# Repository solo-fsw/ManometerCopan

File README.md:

# ManometerCopan
Manometer for Copan lab

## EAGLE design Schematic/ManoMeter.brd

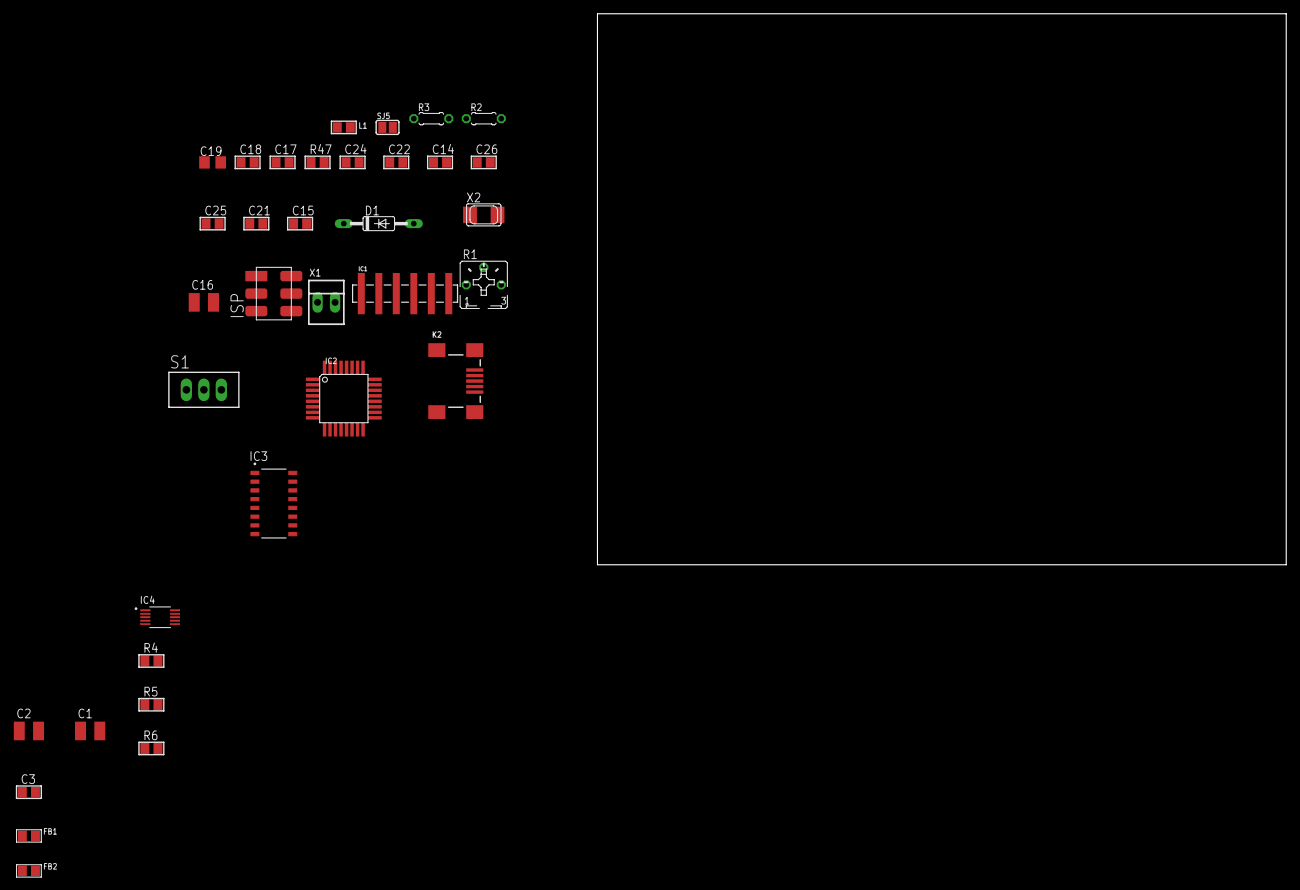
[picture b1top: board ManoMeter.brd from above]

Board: 2 copper layers, 100.0 x 80.0 mm, 35 parts (0 on the bottom side), 26 nets, no tracks yet.

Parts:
C1, C2, C16: 10u; C1210
C3, C14, C22, C24: 100n; C0805
C15, C21, C25, C26: 100N; C0805
C17, C18: 22p; C0805
C19: 10uF; R/2012-12R
D1: 1N4148DO35-10; DO35-10
FB1, FB2: MMZ2012Y152B; 0805
IC1: MPS20N0040D-S; 1X06_SMD_MALE
IC2: ATMEGA328P-32PIN-AU; TQFP32-08
IC3: CH340C; SOIC127P600X180-16N
IC4: ADS1115IDGST; SOP50P490X110-10N
ISP: 2X3P-2.54-SMD
K2: USB_MINI-B_SMT; USB-MINIB
L1: 10uH; 0805@1
R1: 10K; B25P
R2: 390; 0204/5
R3: 1k; 0204/5
R4, R5, R6: 4K7; M0805
R47: 10K; M0805
S1: Manual/Off/Auto; TL3XPO
SJ5: SOLDERJUMPER_REFLOW
X1: 22-23-2021
X2: 16Mhz; NX5032

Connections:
+5V: C1.1, C2.1, C3.2, C14.2, C16.1, C19.+, C22.2, C24.2, FB1.1, FB1.2, IC1.2, IC2.4, IC2.6, IC3.16, IC4.8, ISP.2, L1.2, R1.A, R4.2, R5.2, R6.2, R47.2, SJ5.2
AGND: C1.2, C3.1, FB2.2, IC1.5, IC4.3
GND: C2.2, C14.1, C15.2, C16.2, C17.2, C18.2, C19.-, C21.2, C22.1, C24.1, C26.2, D1.A, FB2.1, IC2.3, IC2.5, IC2.21, IC3.1, IC4.1, ISP.6, K2.GND, K2.S1, K2.S2, K2.S3, K2.S4, R1.E, R3.1, S1.2
unnamed: IC2.32, S1.3
unnamed: IC1.3, IC4.7
unnamed: IC1.1, IC1.6, IC4.6
unnamed: IC2.28, IC4.10, R6.1
unnamed: IC2.27, IC4.9, R5.1
unnamed: IC2.26, IC4.2, R4.1
unnamed: IC2.23, R1.S
unnamed: IC2.1, R2.1
unnamed: R2.2, R3.2
unnamed: D1.C, X1.2
unnamed: IC2.2, S1.1
unnamed: IC3.6, K2.D-
unnamed: C15.1, IC3.4
unnamed: C26.1, IC2.20
unnamed: C25.1, IC3.13
unnamed: IC3.5, K2.D+
unnamed: IC2.31, IC3.3
unnamed: K2.VBUS, SJ5.1
unnamed: C21.1, IC2.18, L1.1
unnamed: IC2.30, IC3.2
unnamed: C18.1, IC2.7, X2.P$2
unnamed: C17.1, IC2.8, X2.P$1
RESET: C25.2, IC2.29, ISP.5, R47.1

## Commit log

2023-07-27 InitialCommit
2023-07-27 InitialFirmwareRelease
2023-07-27 SchematicFinished
2023-07-27 BlusDiodeToegevoegd
2023-11-29 PcbAdded
2023-11-29 ChangedSensorType
2023-11-30 UI start
2023-12-07 Tidy data visualisation
2023-12-07 AddedLibrary
2023-12-07 Included library
2023-12-07 Speed measurements and overpressure alteration
2023-12-07 Correct state keeping
2023-12-07 Pressure scaling
2023-12-07 File naming
2023-12-07 Removed TODO
2023-12-07 Executable creation

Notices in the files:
parts and their libraries:
SparkFun-Connectors: Licensing: Creative Commons ShareAlike 4.0 International - https://creativecommons.org/licenses/by-sa/4.0
microbuilder: This work is placed in the public domain, and may be freely used for commercial and non-commercial work with the following conditions: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
